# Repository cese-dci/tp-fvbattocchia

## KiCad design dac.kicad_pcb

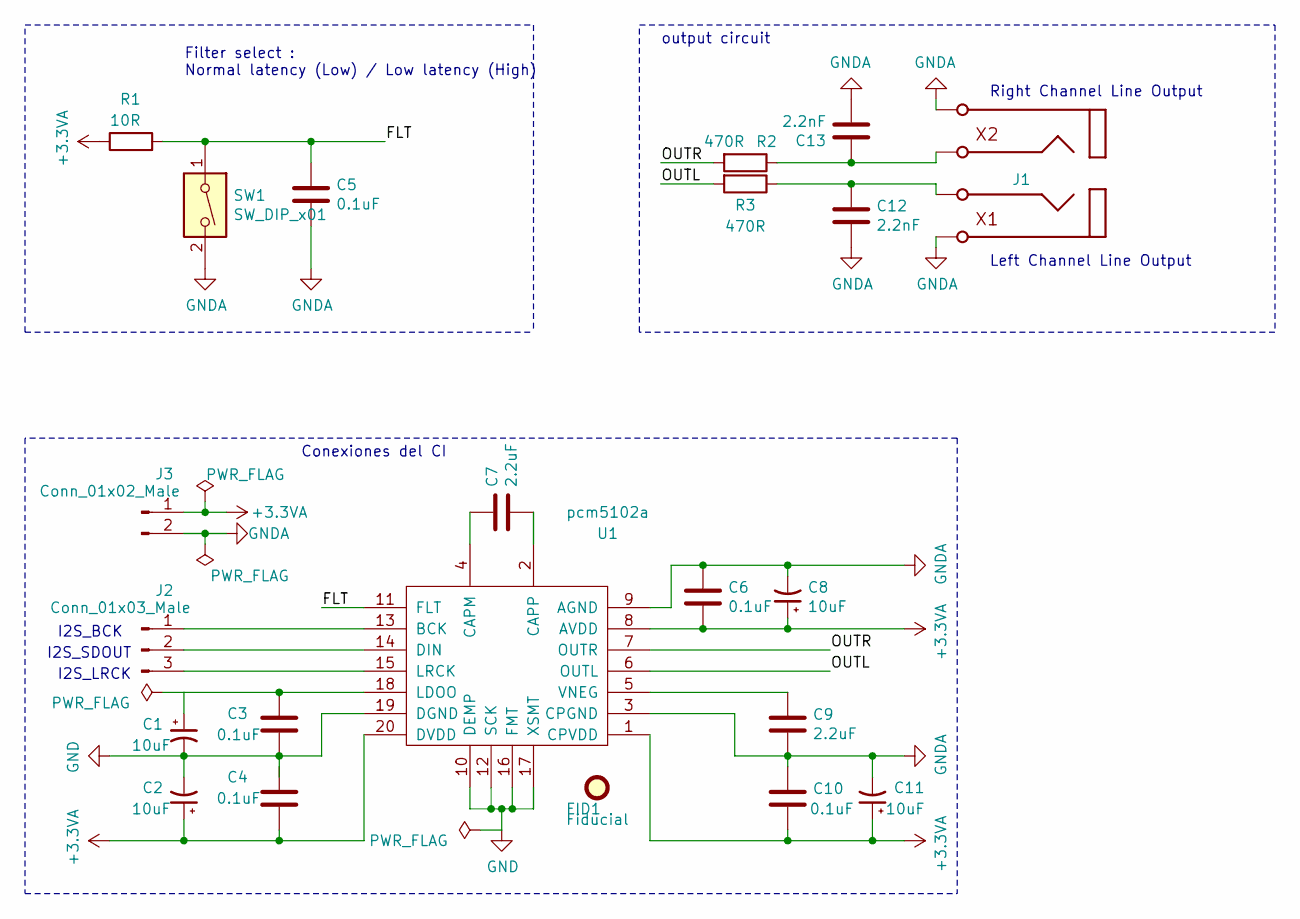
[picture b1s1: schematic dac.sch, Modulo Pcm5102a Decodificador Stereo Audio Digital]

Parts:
C1, C2, C8, C11: 10uF; CP_Radial_D4.0mm_P1.50mm
C3, C4, C5, C6, C10: 0.1uF; C_Disc_D3.8mm_W2.6mm_P2.50mm
C7, C9: 2.2uF; C_Radial_D5.0mm_H7.0mm_P2.00mm
C12, C13: 2.2nF; C_Disc_D3.0mm_W1.6mm_P2.50mm
FID1: Fiducial; Fiducial_0.5mm_Mask1.5mm
J1: RCJ-2121
J2: Conn_01x03_Male; PinHeader_1x03_P2.54mm_Vertical
J3: Conn_01x02_Male; PinHeader_1x02_P2.54mm_Vertical
R1: 10R; R_Axial_DIN0204_L3.6mm_D1.6mm_P5.08mm_Horizontal
R2, R3: 470R; R_Axial_DIN0204_L3.6mm_D1.6mm_P5.08mm_Horizontal
SW1: SW_DIP_x01; SW_DIP_SPSTx01_Slide_6.7x4.1mm_W7.62mm_P2.54mm_LowProfile
U1: pcm5102a; TSSOP-20_4.4x5mm_P0.5mm

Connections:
+3.3VA: C2.1, C4.2, C6.2, C8.1, C10.2, C11.1, J3.1, R1.1, U1.1 (CPVDD), U1.8 (AVDD), U1.20 (DVDD)
/FLT: C5.1, R1.2, SW1.1, U1.11 (FLT)
/OUTL: R3.2, U1.6 (OUTL)
/OUTR: R2.2, U1.7 (OUTR)
GND: C1.2, C2.2, C3.2, C4.1, U1.10 (DEMP), U1.12 (SCK), U1.16 (FMT), U1.17 (XSMT), U1.19 (DGND)
GNDA: C5.2, C6.1, C8.2, C9.2, C10.1, C11.2, C12.2, C13.2, J1.1, J1.3, J3.2, SW1.2, U1.3 (CPGND), U1.9 (AGND)
unnamed: C1.1, C3.1, U1.18 (LDOO)
unnamed: C7.1, U1.4 (CAPM)
unnamed: C7.2, U1.2 (CAPP)
unnamed: C9.1, U1.5 (VNEG)
unnamed: C12.1, J1.2, R3.1
unnamed: C13.1, J1.4, R2.1
unnamed: J2.1, U1.13 (BCK)
unnamed: J2.2, U1.14 (DIN)
unnamed: J2.3, U1.15 (LRCK)

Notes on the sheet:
Right Channel Line Output
Left Channel Line Output
Filter select : Normal latency (Low) / Low latency (High)
output circuit
I2S_LRCK
I2S_SDOUT
I2S_BCK
Conexiones del CI

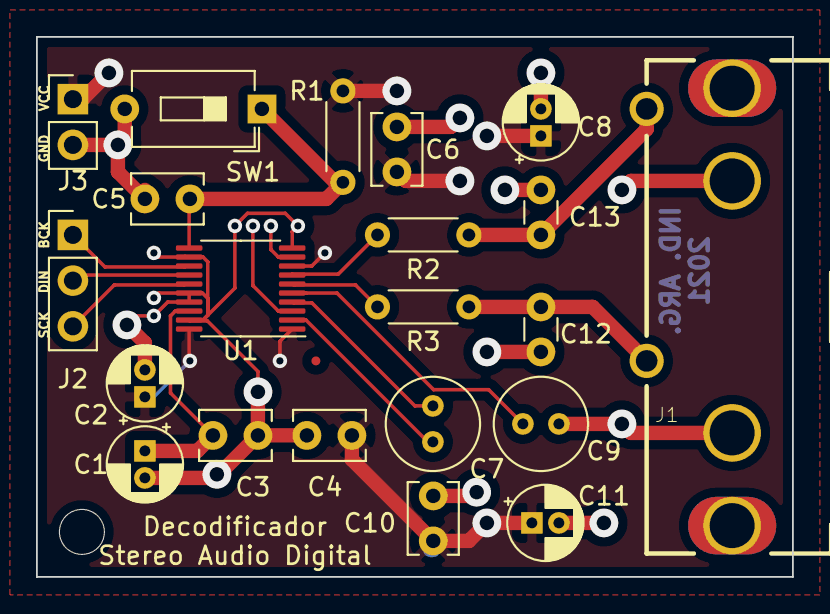
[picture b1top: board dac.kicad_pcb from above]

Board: 2 copper layers, 42.0 x 30.0 mm, 23 parts (0 on the bottom side), 15 nets.

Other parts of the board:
H1: MountingHole; MountingHole_2.5mm

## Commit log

2021-03-16 primer diseño del esquematico
2021-03-19 termine esquematico
2021-03-26 start PCB
2021-03-31 agrego documentacion
2021-04-04 se corrije esquematico y pcb conector RCA, se agrega modelo 3d
2021-04-14 correcciones
2021-04-14 correcciones profe
2021-04-14 ruteo PCB
2021-04-14 se avanza en el pcb
2021-04-16 se agregan comentarios de la clase 7
2021-04-19 correcciones en el esquematico indicadas por el profesor
2021-04-23 pcb terminado
2021-04-28 correcciones pcb

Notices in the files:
dac.kicad_pcb:
Creative Commons Attribution -ShareAlike 4.0 International License
